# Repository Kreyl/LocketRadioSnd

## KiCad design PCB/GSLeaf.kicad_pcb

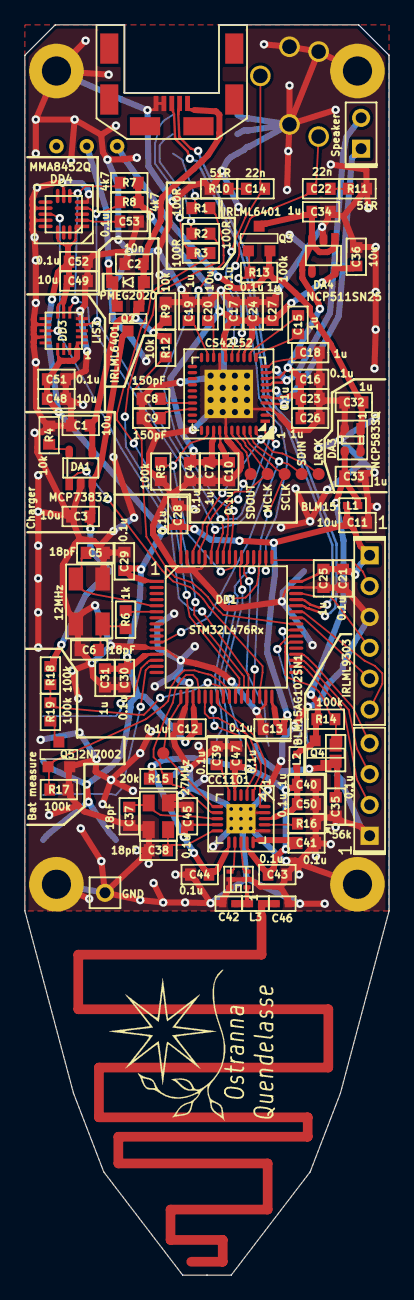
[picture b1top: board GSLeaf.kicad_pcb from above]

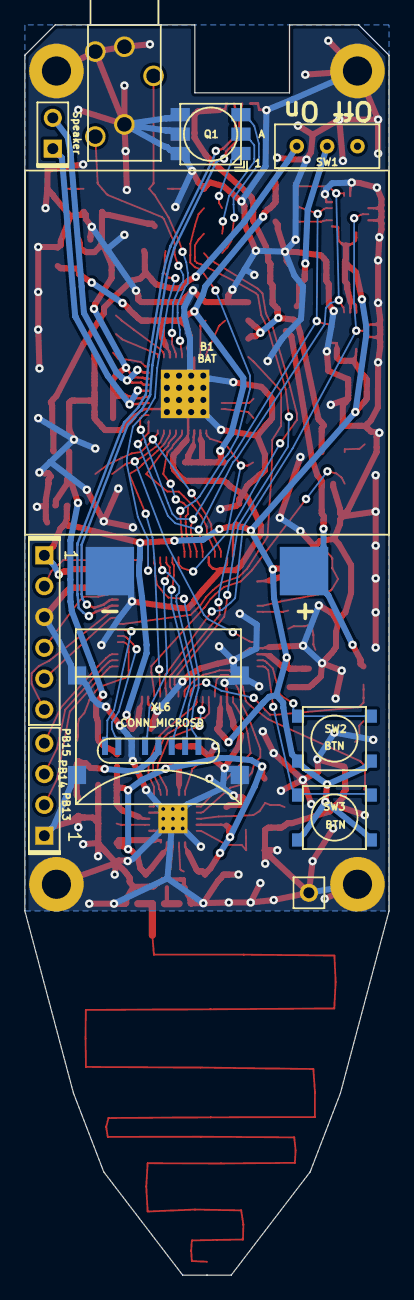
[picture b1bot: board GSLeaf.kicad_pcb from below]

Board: 2 copper layers, 30.0 x 103.0 mm, 116 parts (7 on the bottom side), 81 nets.

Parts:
ANT1: ANT_PCB_MONO; ANT_868_SEIDHE
B1: BAT; EEMB603030
BLN1: BALUN868JOHANSON; BALUN_JOHANSON868
C1, C3, C11, C20, C36, C48, C49: 10u; CAP_0603
C2: 10n; CAP_0603
C4, C10, C12, C13, C16, C17, C21, C23, C24, C28, C29, C30, C35, C39, C41, C43, C44, C45, C47, C50, C51, C52, C53: 0.1u; CAP_0603
C5, C6, C37, C38: 18pF; CAP_0603
C7, C15, C18, C19, C25, C26, C27, C31, C32, C33, C34, C40: 1u; CAP_0603
C8, C9: 150pF; CAP_0603
C14, C22: 22n; CAP_0603
C42, C46: *; CAP_0402
D1: PMEG2020; SOD323
DA1: MCP73832; SOT23-5
DA2: CS42L52; QFN40
DA3: NCP583SQ; SC82AB
DA4: NCP511SN25; SOT23-5
DD1: STM32L476Rx; LQFP64
DD2: CC1101; QFN20
DD3: LIS3; LGA16_3X3_5_3
DD4: MMA8452Q; QFN16_5x3
F1: Fuse0R; RES_0603_FUSE
HOLE1, HOLE2, HOLE3, HOLE4: HOLE_METALLED; Hole2d4_out4d5mm
L1: BLM15; IND_0402
L2: BLM15AG102SN1; IND_0402
L3: *; IND_0402
Logo1: Logo; Ostranna_12d7_10d1
Q1: LED_5050
Q2, Q3: IRLML6401; SOT23-3
Q4: IRLML9303; SOT23-3
Q5: 2N7002; SOT23-3
R1, R2, R3: 100R; RES_0603
R4, R9, R12: 10k; RES_0603
R5, R13, R14, R17, R18, R19: 100k; RES_0603
R6: 1k; RES_0603
R7, R8: 4k7; RES_0603
R10, R11: 51R; RES_0603
R15: 20k; RES_0603
R16: 56k; RES_0603
SW1: SWITCH; SW_SS-1P2T
SW2, SW3: BTN; BTN_4x4_SMD
TP2, TP3, TP4, TP5, TP6, TP7: TESTPOINT; TESTPOINT_1MM
XL1: CONN_6; PLS-6
XL2: USB_MINI_B; USBmicro_MOLEX_WM17142
XL3: CONN_4; PLS-4
XL4: AudioJackSimple; AUDIO_CKX3_5_30
XL5: CONN_2; PLS-2
XL6: CONN_MICROSD; MICROSD_CAP_FIX05A
XL7: CONN_1; PLS-1Rnd
XTAL1: 12MHz; 0503x4-4
XTAL2: 27MHz; 03225C4

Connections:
+3.3V: C33.1, DA3.3, L1.2, L2.2, Q4.2, R14.1
+5V: C1.2, C2.2, D1.A, DA1.4, Q2.1, R9.1, R12.2, XL2.1
+BATT: B1.A, C3.2, DA1.3, Q2.3, R18.1
/ACC_INT1: DD1.28, DD3.11, DD4.11
/ANT1: BLN1.1, C42.1, L3.2
/ANT2: ANT1.1, C46.1, L3.1
/AU_LRCK: DA2.40, DD1.62, TP6.1
/AU_MCLK: DA2.37, DD1.61, TP5.1
/AU_RST: DA2.32, DD1.55, R5.2
/AU_SCLK: DA2.38, DD1.29, TP2.1
/AU_SDIN: DA2.39, DD1.11, TP3.1
/AU_SDOUT: DA2.36, DD1.57, TP4.1
/BAT_MEAS: DD1.24, R18.2, R19.1
/BLUE_LED: DD1.56, R1.2
/BTN_DOWN: DD1.15, SW3.1
/BTN_UP: DD1.14, SW2.1
/CC_CS: DD1.20, DD2.7, R15.1
/CC_GDO0: DD1.17, DD2.6, TP7.1
/CC_MISO: DD1.22, DD2.2
/CC_MOSI: DD1.23, DD2.20
/CC_SCK: DD1.21, DD2.1
/Charge: DA1.1, DD1.30
/D+: DD1.45, XL2.3
/D-: DD1.44, XL2.2
/GREEN_LED: DD1.27, R3.2
/HP_OUTA: C14.2, DA2.15, XL4.2
/HP_OUTB: C22.2, DA2.14, XL4.3
/MEASURE_EN: DD1.25, Q5.1, R17.2
/PWR_CTRLED: C16.1, C23.1, C26.1, C34.1, DA2.5, DA2.8, DA4.1, DA4.3, Q3.3
/PWR_EN: DD1.50, Q3.1, R13.1
/PWR_UNST_ALWAYS: D1.C, Q2.2, SW1.2
/RED_LED: DD1.26, R2.2
/RF1: BLN1.4, DD2.12
/RF2: BLN1.3, DD2.13
/SCL: DA2.2, DD1.58, DD3.4, DD4.4, R8.1
/SDA: DA2.1, DD1.59, DD3.6, DD4.6, R7.1
/SD_CLK: DD1.53, XL6.5
/SD_CMD: DD1.54, XL6.3
/SD_DAT0: DD1.39, XL6.7
/SD_DAT1: DD1.40, XL6.8
/SD_DAT2: DD1.51, XL6.1
/SD_DAT3: DD1.52, XL6.2
/SD_PWR: C35.1, F1.1, Q4.3, XL6.4
/SD_PWR_EN: DD1.38, F1.2, Q4.1, R14.2
/SPK_M: DA2.7, DA2.9, XL5.2
/SPK_P: DA2.4, DA2.6, XL5.1
/SWCLK: DD1.49, XL1.2
/SWDIO: DD1.46, XL1.4
/UART_RX: DD1.43, XL1.6
/UART_TX: DD1.42, XL1.5
GND: B1.C, BLN1.2, BLN1.5, BLN1.6, C1.1, C2.1, C3.1, C4.2, C5.2, C6.2, C7.2, C8.1, C9.1, C10.2, C11.1, C12.1, C13.1, C16.2, C17.2, C18.1, C19.1, C20.1, C21.1, C23.2, C24.2, C25.1, C26.2, C27.2, C28.1, C29.1, C30.1, C31.1, C32.2, C33.2, C34.2, C35.2, C36.2, C37.2, C38.2, C39.1, C40.2, C41.2, C42.2, C43.2, C44.2, C45.2, C46.2, C47.2, C48.2, C49.2, C50.2, C51.2, C52.2, C53.2, DA1.2, DA2.3, DA2.17, DA2.35, DA2.PAD, DA3.2, DA4.2, DD1.12, DD1.18, DD1.31, DD1.47, DD1.60, DD1.63, DD2.16, DD2.19, DD2.PAD, DD3.5, DD3.10, DD3.12, DD4.5, DD4.7, DD4.10, DD4.12, HOLE1.H, HOLE2.H, HOLE3.H, HOLE4.H, Q1.4, Q1.5, Q1.6, Q5.2, R4.2, R5.1, R9.2, R10.1, R11.1, R16.2, R17.1, XL1.3, XL2.4, XL2.5, XL3.1, XL4.1, XL4.H, XL6.6, XL6.H, XL7.1, XTAL1.H, XTAL2.H
unnamed: C5.1, DD1.5, XTAL1.1
unnamed: C6.1, R6.1, XTAL1.2
unnamed: C8.2, DA2.27
unnamed: C9.2, DA2.28
unnamed: C14.1, R10.2
unnamed: C15.1, DA2.11
unnamed: C15.2, DA2.12
unnamed: C18.2, DA2.10
unnamed: C19.2, DA2.19
unnamed: C20.2, DA2.18
unnamed: C22.1, R11.2
unnamed: C37.1, DD2.8, XTAL2.1
unnamed: C38.1, DD2.10, XTAL2.2
unnamed: C39.2, DD2.5
unnamed: C53.1, DD4.2
unnamed: DA1.5, R4.1
unnamed: DD1.6, R6.2
unnamed: DD1.34, XL3.2
unnamed: DD1.35, XL3.3
unnamed: DD1.36, XL3.4
unnamed: DD1.41, R12.1
unnamed: DD2.17, R16.1
unnamed: Q1.1, R1.1
unnamed: Q1.2, R2.1
unnamed: Q1.3, R3.1
unnamed: Q5.3, R19.2
PwrMCU: C11.2, C12.2, C13.2, C21.2, C25.2, C28.2, C29.2, C30.2, C31.2, C48.1, C49.1, C51.1, C52.1, DD1.1, DD1.13, DD1.19, DD1.32, DD1.48, DD1.64, DD3.1, DD3.7, DD3.8, DD3.14, DD4.1, DD4.14, L1.1, SW2.2, SW3.2, XL1.1
PwrUnst: C32.1, DA3.1, DA3.4, Q3.2, R13.2, SW1.1
VAA: C4.1, C7.1, C10.1, C17.1, C24.1, C27.1, C36.1, DA2.13, DA2.16, DA2.33, DA2.34, DA4.5, R7.2, R8.2
VCC: C40.1, C41.1, C43.1, C44.1, C45.1, C47.1, C50.1, DD2.4, DD2.9, DD2.11, DD2.14, DD2.15, DD2.18, L2.1, R15.2

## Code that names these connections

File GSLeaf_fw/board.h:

/*
 * board.h
 *
 *  Created on: 12 ����. 2015 �.
 *      Author: Kreyl
 */

#ifndef BOARD_H__
#define BOARD_H__

// ==== General ====
#define BOARD_NAME          "GSLeaf01"
#define APP_NAME            "SpeakingStone w Radio"

// MCU type as defined in the ST header.
#define STM32L476xx

// Freq of external crystal if any. Leave it here even if not used.
#define CRYSTAL_FREQ_HZ         12000000

// OS timer settings
#define STM32_ST_IRQ_PRIORITY   9
#define STM32_ST_USE_TIMER      5
#define STM32_TIMCLK1           (Clk.APB1FreqHz)    // Timer 5 is clocked by APB1

//  Periphery
#define I2C1_ENABLED            TRUE
#define I2C2_ENABLED            FALSE
#define I2C3_ENABLED            FALSE
#define SIMPLESENSORS_ENABLED   FALSE
#define BUTTONS_ENABLED         FALSE

#define ACC_REQUIRED            FALSE

#define ADC_REQUIRED            FALSE
#define STM32_DMA_REQUIRED      TRUE    // Leave this macro name for OS

#if 1 // ========================== GPIO =======================================
// EXTI
#define INDIVIDUAL_EXTI_IRQ_REQUIRED    FALSE

// Buttons
#define BTN1_PIN        GPIOA, 0, pudPullDown
#define BTN2_PIN        GPIOA, 1, pudPullDown

// UART
#define UART_TX_PIN     GPIOA, 9
#define UART_RX_PIN     GPIOA, 10

// RGB LED
#define LED_BLUE_CH     { GPIOB, 4, TIM3, 1, invNotInverted, omPushPull, 255 }
#define LED_GREEN_CH    { GPIOB, 1, TIM3, 4, invNotInverted, omPushPull, 255 }
#define LED_RED_CH      { GPIOB, 0, TIM3, 3, invNotInverted, omPushPull, 255 }

// PWR_EN
#define PWR_EN_PIN      GPIOA, 15, omPushPull
// Charge
#define CHARGE_PIN      GPIOB, 11, pudPullUp

// CS42L52
#define AU_RESET        GPIOB, 3, omPushPull
#define AU_SDIN         GPIOC, 3, omPushPull, pudNone, AF13 // MOSI; SAI1_A
#define AU_SDOUT        GPIOB, 5, omPushPull, pudNone, AF13 // MISO; SAI1_B
#define AU_MCLK         GPIOB, 8, omPushPull, pudNone, AF13
#define AU_MCLK_TIM     GPIOB, 8, TIM4, 3, invNotInverted, omPushPull, 1
#define AU_LRCK         GPIOB, 9, omPushPull, pudNone, AF13
#define AU_SCLK         GPIOB, 10, omPushPull, pudNone, AF13
#define AU_i2c          i2c1
#define AU_SAI          SAI1
#define AU_SAI_A        SAI1_Block_A
#define AU_SAI_B        SAI1_Block_B
#define AU_SAI_RccEn()  RCC->APB2ENR |= RCC_APB2ENR_SAI1EN
#define AU_SAI_RccDis() RCC->APB2ENR &= ~RCC_APB2ENR_SAI1EN
//#define AU_SAI_RccRst() RCC->APB2RSTR = RCC_APB2RSTR_SAI1RST

// Acc
#define Acc_i2c         i2c1
#define ACC_IRQ_GPIO    GPIOB
#define ACC_IRQ_PIN     2

// I2C
#define I2C1_GPIO       GPIOB
#define I2C1_SCL        6
#define I2C1_SDA        7
#define I2C2_GPIO       GPIOB
#define I2C2_SCL        10
#define I2C2_SDA        11
#define I2C3_GPIO       GPIOC
#define I2C3_SCL        0
#define I2C3_SDA        1
// I2C Alternate Function
#define I2C_AF          AF4

// SD
#define SD_PWR_PIN      GPIOC, 7
#define SD_AF           AF12
#define SD_DAT0         GPIOC,  8, omPushPull, pudPullUp, SD_AF
#define SD_DAT1         GPIOC,  9, omPushPull, pudPullUp, SD_AF
#define SD_DAT2         GPIOC, 10, omPushPull, pudPullUp, SD_AF
#define SD_DAT3         GPIOC, 11, omPushPull, pudPullUp, SD_AF
#define SD_CLK          GPIOC, 12, omPushPull, pudNone,   SD_AF
#define SD_CMD          GPIOD,  2, omPushPull, pudPullUp, SD_AF

// Radio: SPI, PGpio, Sck, Miso, Mosi, Cs, Gdo0
#define CC_Setup0       SPI1, GPIOA, 5,6,7, GPIOA,4, GPIOA,3

#endif // GPIO

#if 1 // =========================== I2C =======================================
// i2cclkPCLK1, i2cclkSYSCLK, i2cclkHSI
#define I2C_CLK_SRC     i2cclkHSI
#define I2C_BAUDRATE_HZ 400000
#endif

#if ADC_REQUIRED // ======================= Inner ADC ==========================
// Clock divider: clock is generated from the APB2
#define ADC_CLK_DIVIDER		adcDiv2

// ADC channels
#define ADC_BATTERY_CHNL 	14
// ADC_VREFINT_CHNL
#define ADC_CHANNELS        { ADC_BATTERY_CHNL, ADC_VREFINT_CHNL }
#define ADC_CHANNEL_CNT     2   // Do not use countof(AdcChannels) as preprocessor does not know what is countof => cannot check
#define ADC_SAMPLE_TIME     ast24d5Cycles
#define ADC_OVERSAMPLING_RATIO  64   // 1 (no oversampling), 2, 4, 8, 16, 32, 64, 128, 256
#endif

#if 1 // =========================== DMA =======================================
#define STM32_DMA_REQUIRED  TRUE
// ==== Uart ====
#define UART_DMA_TX_MODE(Chnl) (STM32_DMA_CR_CHSEL(Chnl) | DMA_PRIORITY_LOW | STM32_DMA_CR_MSIZE_BYTE | STM32_DMA_CR_PSIZE_BYTE | STM32_DMA_CR_MINC | STM32_DMA_CR_DIR_M2P | STM32_DMA_CR_TCIE)
#define UART_DMA_RX_MODE(Chnl) (STM32_DMA_CR_CHSEL(Chnl) | DMA_PRIORITY_MEDIUM | STM32_DMA_CR_MSIZE_BYTE | STM32_DMA_CR_PSIZE_BYTE | STM32_DMA_CR_MINC | STM32_DMA_CR_DIR_P2M | STM32_DMA_CR_CIRC)
#define UART_DMA_TX     STM32_DMA_STREAM_ID(1, 4)
#define UART_DMA_RX     STM32_DMA_STREAM_ID(1, 5)
#define UART_DMA_CHNL   2

// ==== I2C ====
#define I2C1_DMA_TX     STM32_DMA_STREAM_ID(2, 7)
#define I2C1_DMA_RX     STM32_DMA_STREAM_ID(2, 6)
#define I2C1_DMA_CHNL   5
#define I2C2_DMA_TX     STM32_DMA_STREAM_ID(1, 4)
#define I2C2_DMA_RX     STM32_DMA_STREAM_ID(1, 5)
#define I2C2_DMA_CHNL   3
#define I2C3_DMA_TX     STM32_DMA_STREAM_ID(1, 2)
#define I2C3_DMA_RX     STM32_DMA_STREAM_ID(1, 3)
#define I2C3_DMA_CHNL   3

// ==== SAI ====
#define SAI_DMA_A       STM32_DMA_STREAM_ID(2, 1)
#define SAI_DMA_B       STM32_DMA_STREAM_ID(2, 2)
#define SAI_DMA_CHNL    1

// ==== SDMMC ====
#define STM32_SDC_SDMMC1_DMA_STREAM   STM32_DMA_STREAM_ID(2, 5)

#if ADC_REQUIRED
#define ADC_DMA         STM32_DMA1_STREAM1
#define ADC_DMA_MODE    STM32_DMA_CR_CHSEL(0) |   /* DMA1 Stream1 Channel0 */ \
                        DMA_PRIORITY_LOW | \
                        STM32_DMA_CR_MSIZE_HWORD | \
                        STM32_DMA_CR_PSIZE_HWORD | \
                        STM32_DMA_CR_MINC |       /* Memory pointer increase */ \
                        STM32_DMA_CR_DIR_P2M |    /* Direction is peripheral to memory */ \
                        STM32_DMA_CR_TCIE         /* Enable Transmission Complete IRQ */
#endif // ADC

#endif // DMA

#if 1 // ========================== USART ======================================
#define PRINTF_FLOAT_EN FALSE
#define UART_TXBUF_SZ   512
#define UART_RXBUF_SZ   256
#define CMD_BUF_SZ      256

#define CMD_UART        USART1

#define CMD_UART_PARAMS \
    CMD_UART, UART_TX_PIN, UART_RX_PIN, \
    UART_DMA_TX, UART_DMA_RX, UART_DMA_TX_MODE(UART_DMA_CHNL), UART_DMA_RX_MODE(UART_DMA_CHNL), \
    uartclkHSI // Use independent clock

#endif

#endif //BOARD_H__

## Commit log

2022-05-25 master
2022-05-26 Sound do not work
2022-05-26 Stone release
2022-08-03 + ID==0xFF means stop
2022-08-03 + Acc
2022-08-04 * Switch to FrenchBottle motion algo + Read setting from settings.ini
2022-08-07 Acc + Radio RC
2023-07-04 pragma once replaced with ifdef
2023-07-06 Logic seems implemented
2023-07-08 Release
2024-07-29 Newer KiCAD
2024-07-29 Switch to Eclipse
2025-08-10 All ok. Actual code moved to Locket folder.
